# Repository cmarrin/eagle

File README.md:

# eagle

All my [Eagle](https://www.autodesk.com/products/eagle/overview) projects and libraries

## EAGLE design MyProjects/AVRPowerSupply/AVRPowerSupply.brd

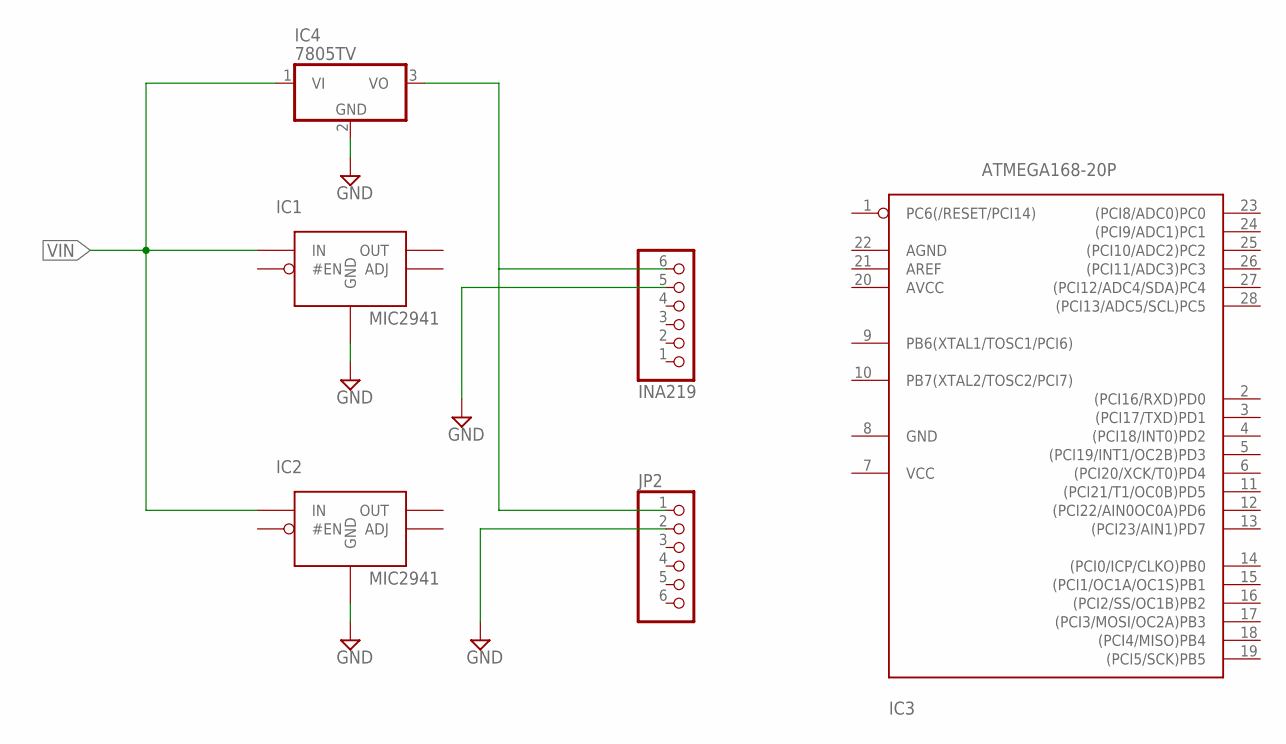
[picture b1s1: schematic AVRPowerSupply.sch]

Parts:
IC1, IC2: BBSUP_MIC2941; BBSUP_TO220-5
IC3: ATMEGA168-20P; DIL28-3
IC4: 7805TV; TO220V
INA219: PINHD-1X6; 1X06
JP2: PINHD-1X6; 1X06

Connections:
GND: IC1.3 (GND), IC2.3 (GND), IC4.2 (GND), INA219.5, JP2.2
INA219: IC4.3 (VO), INA219.6, JP2.1
VIN: IC1.4 (IN), IC2.4 (IN), IC4.1 (VI)

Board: 2 copper layers, 6 parts (0 on the bottom side), 3 nets, no tracks yet.

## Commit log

2017-12-06 initial checkin of existing files
2017-12-08 Office Clock WIP
2017-12-20 Updates to Office Clock
